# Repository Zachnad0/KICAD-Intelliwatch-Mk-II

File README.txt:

Intelliwatch Mk II

=== Operational Features ===
Internet Connection Required:
	Update internal date & time (automatic, whenever connection established)
	Obtain and display current stock values (manual update request)
	(?? google API) Show next #n google calendar events (A/B scroll up/down)
	(?? do last if at all) Google tasks integration (manual update request)
	Show weather for next 24 hours, very simple (mode, A/B scroll left/right)

Functions & Software Modes:
	Toggle time 7-seg disp. by displaying no digits (mode, A/B key)
	[X] replaced by switch - "off-mode" of LCD display (just a mode, makes LCD LED pin switch by p-MOS)
	QMC5883L Compass Mode shows current heading (mode, A/B keys change inclination temporarily, but that is not saved)
	ADC voltmeter/osc-scope (mode)
	(?? SD-card reading must be used) Cat Picture Mode cycle through pics on SD card (mode, A/B change pic)
	Torch Mode (A/B key inc/dec brightness in 3 steps, auto turn off on mode change)

=== Main Specs ===
Supply voltage: 
	>> Standard DC Barrel Jack << (can connect to any >=6V supply effectively)
	Seperate unit containing 2-4x 3.7V Li-ion rechargeable cells

Visual Displays and Indicators:
	1.8'' TFT LCD display (I2C)
	4-digit 7-segment display (I2C)
	SMD LEDs in series with keyswitches, and more for power and etc.

Controls:
	4x cherry-mx keyswitches
	standard power switch

=== Mk III+ Possible Features ===
Resistance Measuring Mode!!! color bands as rectangles on LCD (mode, A/B shows raw/E12)
Digitally-tuned radio receiver?
Mains AC power in (dangerous???)
Li-Ion cells charging circuit and 12V DC cable power in.
Snapper Card Holder/deployer??? (mode, A/B extend/retract)

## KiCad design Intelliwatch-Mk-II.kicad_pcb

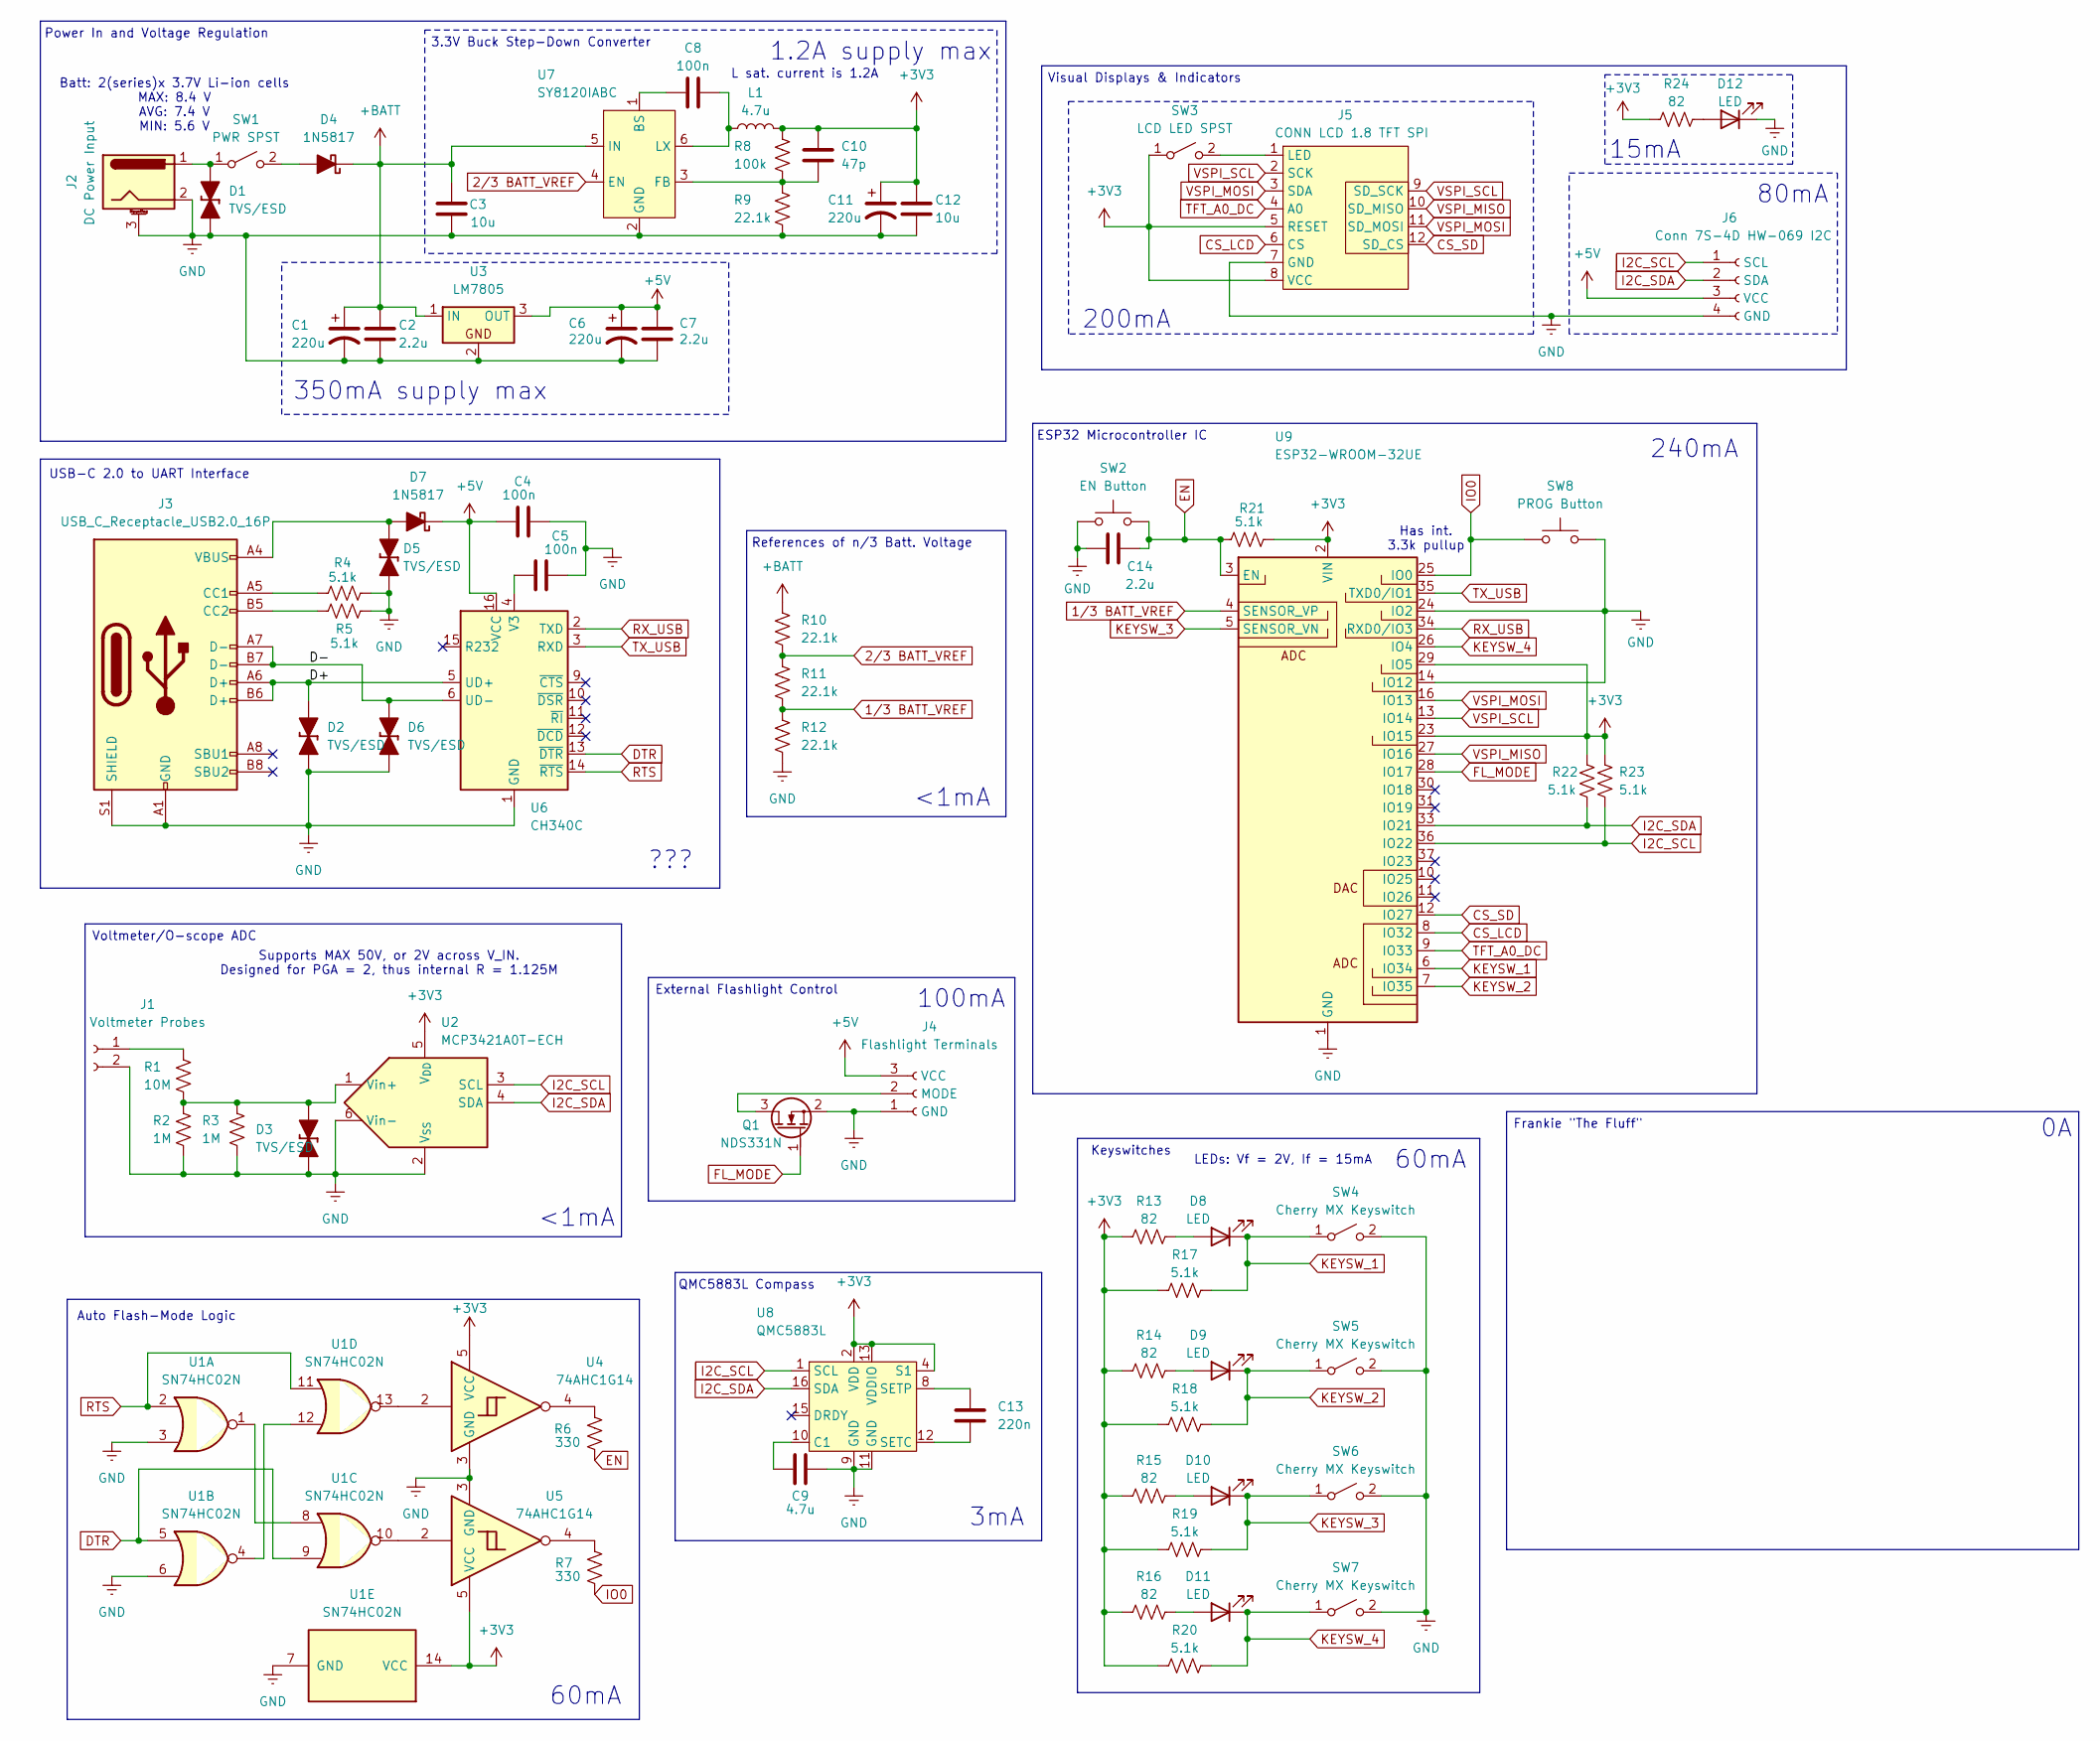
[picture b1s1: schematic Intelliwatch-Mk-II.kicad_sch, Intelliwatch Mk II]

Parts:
C1, C6, C11: 220u; CP_Radial_D6.3mm_P2.50mm; LCSC Part # n/a
C2, C7, C14: 2.2u; C_0603_1608Metric; LCSC Part # C415535
C3, C12: 10u; C_0805_2012Metric; LCSC Part # C440198
C4, C5, C8: 100n; C_1206_3216Metric; LCSC Part # C97946
C9: 4.7u; C_0805_2012Metric; LCSC Part # C437557
C10: 47p; C_0603_1608Metric; LCSC Part # C882552
C13: 220n; C_1206_3216Metric; LCSC Part # C161277
D1, D2, D3, D5, D6: TVS/ESD; D_SOD-323_TVS; LCSC Part # C5180217
D4, D7: 1N5817; D_A-405_P10.16mm_Horizontal; LCSC Part # n/a
D8, D9, D10, D11, D12: LED; LED_0603_1608Metric; LCSC Part # C497928
J1: Voltmeter Probes; Standard IO Holes; LCSC Part # n/a
J2: DC Power Input; BarrelJack_Horizontal; LCSC Part # C720557
J3: USB_C_Receptacle_USB2.0_16P; USB_C_Receptacle_G-Switch_GT-USB-7010ASV; LCSC Part # C2988369
J4: Flashlight Terminals; PinSocket_1x03_P2.54mm_Vertical; LCSC Part # n/a
J5: CONN LCD 1.8 TFT SPI; Conn 1.8 TFT LCD SPI; LCSC Part # n/a
J6: Conn 7S-4D HW-069 I2C; LCSC Part # n/a
L1: 4.7u; L_7.3x7.3_H3.5; LCSC Part # C136201
Q1: NDS331N; SuperSOT-3; LCSC Part # C192741
R1: 10M; Fav Res Axial 10.16mm; LCSC Part # C5200509
R2, R3: 1M; Fav Res Axial 10.16mm; LCSC Part # n/a
R4, R5, R17, R18, R19, R20, R21, R22, R23: 5.1k; R_0603_1608Metric; LCSC Part # C318133
R6, R7: 330; R_0603_1608Metric; LCSC Part # C384242
R8: 100k; R_0603_1608Metric; LCSC Part # C25803
R9, R10, R11, R12: 22.1k; R_0603_1608Metric; LCSC Part # C5382621
R13, R14, R15, R16, R24: 82; R_0603_1608Metric; LCSC Part # C861575
SW1: PWR SPST; Standard IO Holes; LCSC Part # n/a
SW2: EN Button; SW_101-C-W_XKB; LCSC Part # C318938
SW3: LCD LED SPST; Standard IO Holes; LCSC Part # n/a
SW4, SW5, SW6, SW7: Cherry MX Keyswitch; SW_Cherry_MX_1.00u_Plate; LCSC Part # n/a
SW8: PROG Button; SW_101-C-W_XKB; LCSC Part # C318938
U1: SN74HC02N; DIP-14_W7.62mm; LCSC Part # C2897
U2: MCP3421A0T-ECH; SOT-23-6; LCSC Part # C29454
U3: LM7805; TO-220-3_Vertical; LCSC Part # n/a
U4, U5: 74AHC1G14; SOT-353_SC-70-5_BigPads; LCSC Part # C3272823
U6: CH340C; SOP-16_4.55x10.3mm_P1.27mm; LCSC Part # C84681
U7: SY8120IABC; SOT-23-6; LCSC Part # C479076
U8: QMC5883L; LGA-16_3x3mm_P0.5mm; LCSC Part # C976032
U9: ESP32-WROOM-32UE; LCSC Part # C701346

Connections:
1/3 BATT_VREF: R11.2, R12.1, U9.4 (SENSOR_VP)
2/3 BATT_VREF: R10.2, R11.1, U7.4 (EN)
+3V3: C10.1, C11.1, C12.1, J5.5 (RESET), J5.8 (VCC), L1.2, R8.1, R13.2, R14.2, R15.2, R16.2, R17.2, R18.2, R19.2, R20.2, R21.1, R22.1, R23.1, R24.1, SW3.1 (A), U1.14 (VCC), U2.5 (V_{DD}), U4.5 (VCC), U5.5 (VCC), U8.2 (VDD), U8.4 (S1), U8.13 (VDDIO), U9.2 (VIN), U9.23 (IO15), U9.29 (IO5)
+5V: C4.1, C6.1, C7.1, D7.1 (K), J4.3 (VCC), J6.3 (VCC), U3.3 (OUT), U6.16 (VCC)
+BATT: C1.1, C2.1, C3.1, D4.1 (K), R10.1, U3.1 (IN), U7.5 (IN)
/D+: D2.1 (K), J3.A6 (D+), J3.B6 (D+), U6.5 (UD+)
/D-: D6.1 (K), J3.A7 (D-), J3.B7 (D-), U6.6 (UD-)
CS_LCD: J5.6 (CS), U9.8 (IO32)
CS_SD: J5.12 (SD_CS), U9.12 (IO27)
DTR: U1.5, U1.9, U6.13 (~DTR)
EN: C14.1, R6.1, R21.2, SW2.2, U9.3 (EN)
FL_MODE: Q1.1 (G), U9.28 (IO17)
GND: C1.2, C2.2, C3.2, C4.2, C5.2, C6.2, C7.2, C9.2, C11.2, C12.2, C14.2, D1.2 (A), D2.2 (A), D3.2 (A), D5.2 (A), D6.2 (A), D12.1 (K), J1.2, J2.2, J2.3 (MountPin), J3.A1 (GND), J3.A12 (GND), J3.B1 (GND), J3.B12 (GND), J3.S1 (SHIELD), J4.1 (GND), J5.7 (GND), J6.4 (GND), Q1.2 (S), R2.2, R3.2, R4.2, R5.2, R9.2, R12.2, SW2.1, SW4.2 (B), SW5.2 (B), SW6.2 (B), SW7.2 (B), SW8.2, U1.3, U1.6, U1.7 (GND), U2.2 (V_{SS}), U2.6 (Vin-), U3.2, U4.3 (GND), U5.3 (GND), U6.1 (GND), U7.2 (GND), U8.9 (GND), U8.11 (GND), U9.1 (GND), U9.14 (IO12), U9.15 (GND), U9.24 (IO2), U9.38 (GND), U9.39 (GND)
I2C_SCL: J6.1 (SCL), R23.2, U2.3 (SCL), U8.1 (SCL), U9.36 (IO22)
I2C_SDA: J6.2 (SDA), R22.2, U2.4 (SDA), U8.16 (SDA), U9.33 (IO21)
IO0: R7.2, SW8.1, U9.25 (IO0)
KEYSW_1: D8.1 (K), R17.1, SW4.1 (A), U9.6 (IO34)
KEYSW_2: D9.1 (K), R18.1, SW5.1 (A), U9.7 (IO35)
KEYSW_3: D10.1 (K), R19.1, SW6.1 (A), U9.5 (SENSOR_VN)
KEYSW_4: D11.1 (K), R20.1, SW7.1 (A), U9.26 (IO4)
unnamed: D1.1 (K), J2.1, SW1.1 (A)
unnamed: D3.1 (K), R1.1, R2.1, R3.1, U2.1 (Vin+)
unnamed: D4.2 (A), SW1.2 (B)
unnamed: D5.1 (K), D7.2 (A), J3.A4 (VBUS), J3.A9 (VBUS), J3.B4 (VBUS), J3.B9 (VBUS)
unnamed: D8.2 (A), R13.1
unnamed: D9.2 (A), R14.1
unnamed: D10.2 (A), R15.1
unnamed: D11.2 (A), R16.1
unnamed: D12.2 (A), R24.2
unnamed: J1.1, R1.2
unnamed: J3.A5 (CC1), R4.1
unnamed: J3.B5 (CC2), R5.1
unnamed: J4.2 (MODE), Q1.3 (D)
unnamed: J5.1 (LED), SW3.2 (B)
unnamed: R6.2, U4.4
unnamed: R7.1, U5.4
unnamed: U1.1, U1.8
unnamed: U1.10, U5.2
unnamed: U1.4, U1.12
unnamed: U1.13, U4.2
unnamed: C5.1, U6.4 (V3)
unnamed: C8.1, U7.1 (BS)
unnamed: C10.2, R8.2, R9.1, U7.3 (FB)
unnamed: C8.2, L1.1, U7.6 (LX)
unnamed: C9.1, U8.10 (C1)
unnamed: C13.2, U8.12 (SETC)
unnamed: C13.1, U8.8 (SETP)
RTS: U1.2, U1.11, U6.14 (~RTS)
RX_USB: U6.2 (TXD), U9.34 (RXD0/IO3)
TFT_A0_DC: J5.4 (A0), U9.9 (IO33)
TX_USB: U6.3 (RXD), U9.35 (TXD0/IO1)
VSPI_MISO: J5.10 (SD_MISO), U9.27 (IO16)
VSPI_MOSI: J5.3 (SDA), J5.11 (SD_MOSI), U9.16 (IO13)
VSPI_SCL: J5.2 (SCK), J5.9 (SD_SCK), U9.13 (IO14)

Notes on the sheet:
Power In and Voltage Regulation
Batt: 2(series)x 3.7V Li-ion cells MAX: 8.4 V AVG: 7.4 V MIN: 5.6 V
60mA
Voltmeter/O-scope ADC
240mA
References of n/3 Batt. Voltage
350mA supply max
200mA
ESP32 Microcontroller IC
Visual Displays & Indicators
100mA
L sat. current is 1.2A
Auto Flash-Mode Logic
Supports MAX 50V, or 2V across V_IN. Designed for PGA = 2, thus internal R = 1.125M
80mA
LEDs: Vf = 2V, If = 15mA
15mA
USB-C 2.0 to UART Interface
1.2A supply max
???
<1mA
3.3V Buck Step-Down Converter
<1mA
Keyswitches
Frankie "The Fluff"
3mA
Has int. 3.3k pullup
External Flashlight Control
QMC5883L Compass

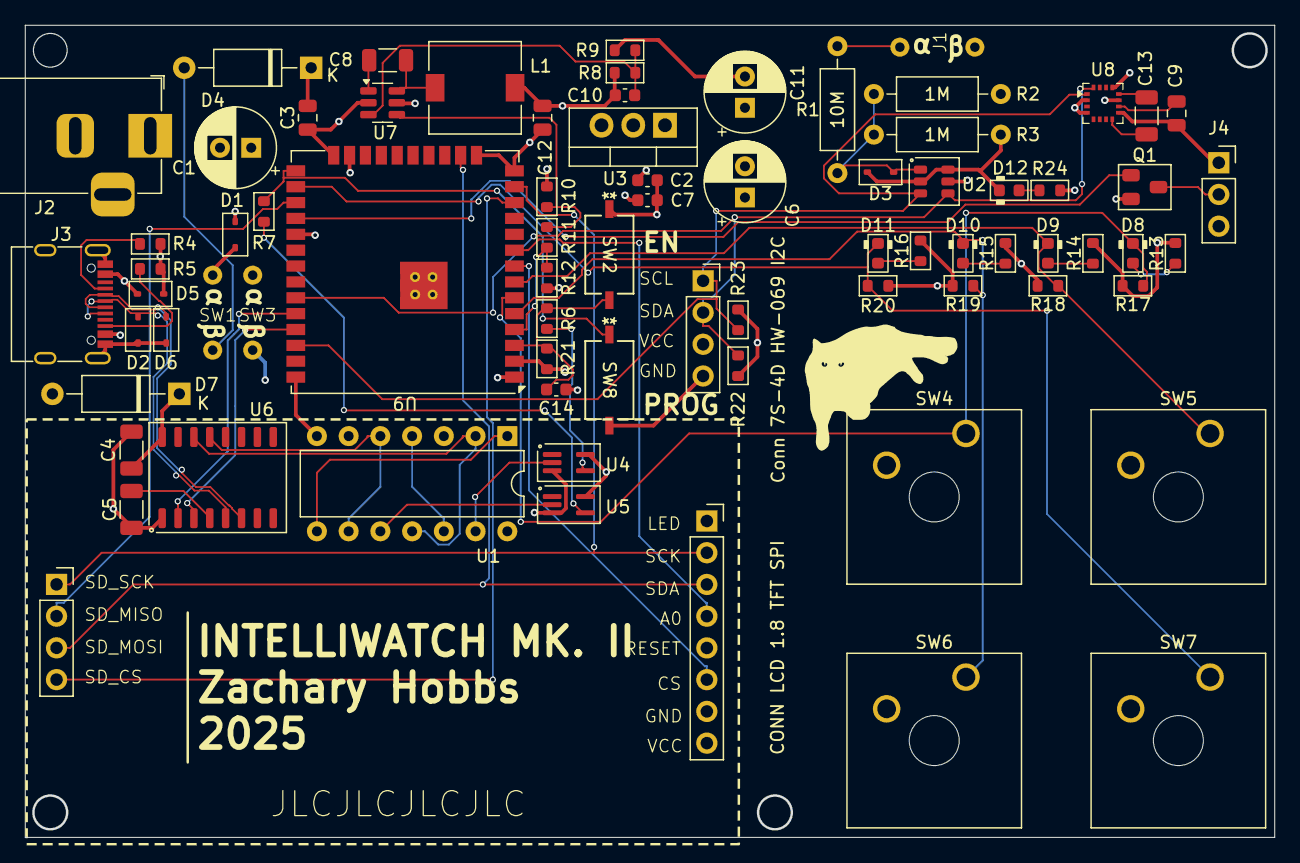
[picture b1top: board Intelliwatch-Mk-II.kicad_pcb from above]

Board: 4 copper layers, 100.0 x 65.0 mm, 75 parts (0 on the bottom side), 54 nets.

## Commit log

2024-11-15 Project files initialized
2024-11-23 ADDED README.txt containing plan for features and etcetera
2024-11-29 WIP op-amp voltage comparator for battery level checking
2024-12-31 connected USB-C to SERIAL-UART adapter.
2025-01-02 ADDED QMC5883L IC, imported, then assigned some footprints
2025-01-16 Made capacitor values more uniform. TODO is add auto-flash support from DTR and RTS pins on SERIAL-UART converter IC.
2025-01-20 ADDED all the damn logic for automatically pulling the EN and IO0 pins into flash-mode on the ESP32 depending on RTS and DTR serial signals.
2025-01-22 ADDED cap to EN pin. ADDED 1.8 TFT SPI LCD with p-MOS on LED pin. TODO connect correct GPIOs to the SPI LCD
2025-01-24 ADDED connections to both visual displays.
2025-01-26 ADDED keyswitches and found 0603 SMD LED to be used for all other indicators in the project. ADDED connections to MOSFETs too. TODO connect keyswitch outputs to ESP32 GPIO pins.
2025-02-01 ADDED current draw for each component. ADDED flashlight. WIP TODO is sort out whether or not to re-use VSPI MOSI and SCL pins with both LCD and SD card.
2025-02-04 ADDED ADC for voltmeter/o-scope (NO res-measuring in this one). WIP TODO is determine whether or not SD and LCD will share SPI bus. TODO change voltage regulators to IC-controller buck converters.
2025-02-04 ADDED 3.3V step-down switching regulator (buck converter). TODO delete old power setup, but keep 5V regulator because that has low maximum short-term current draw so it's fine.
2025-02-05 ADDED ESD protection diodes. FIXED power supply and voltage regulation. WIP figuring out if shared SPI bus is possible.
2025-02-07 FIXED an ESD diode in the wrong place. ADDED Fluff. MODIFIED drawing sheet. REMOVED extra HSPI bus since SD and LCD can take turns using VSPI. ADDED LCSC Part # field for components.
2025-02-08 WIP adding LCSC Part # fields to parts
2025-02-09 ADDED LCSC part #s for all applicable components except for resistors. TODO WIP add resistor LCSC part #s.
2025-02-10 WIP TODO TFT LCD footprint. ADDED remaining LCSC part numbers. ADDED all basic setup specs and design rules for PCB. TODO is to arrange then route PCB, adding necessary 2.7mm diameter bolt holes.
2025-02-11 ADDED TFT LCD footprint w/clearance. FIXED trace width and clearance. TODO arrange PCB.
2025-02-12 FIXED board dimensions to be within minimum to avoid engineering fee. ADDED traces and copper areas for all power/ground nets. TODO is connecting signal lines, and maybe try using that autorouter plu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
2025-02-14 FIXED ESD/TVS diodes to be a different part with practically identical specs.
2025-02-20 UPDATED project to KiCad 9
2025-04-14 Generated interactive BOM
